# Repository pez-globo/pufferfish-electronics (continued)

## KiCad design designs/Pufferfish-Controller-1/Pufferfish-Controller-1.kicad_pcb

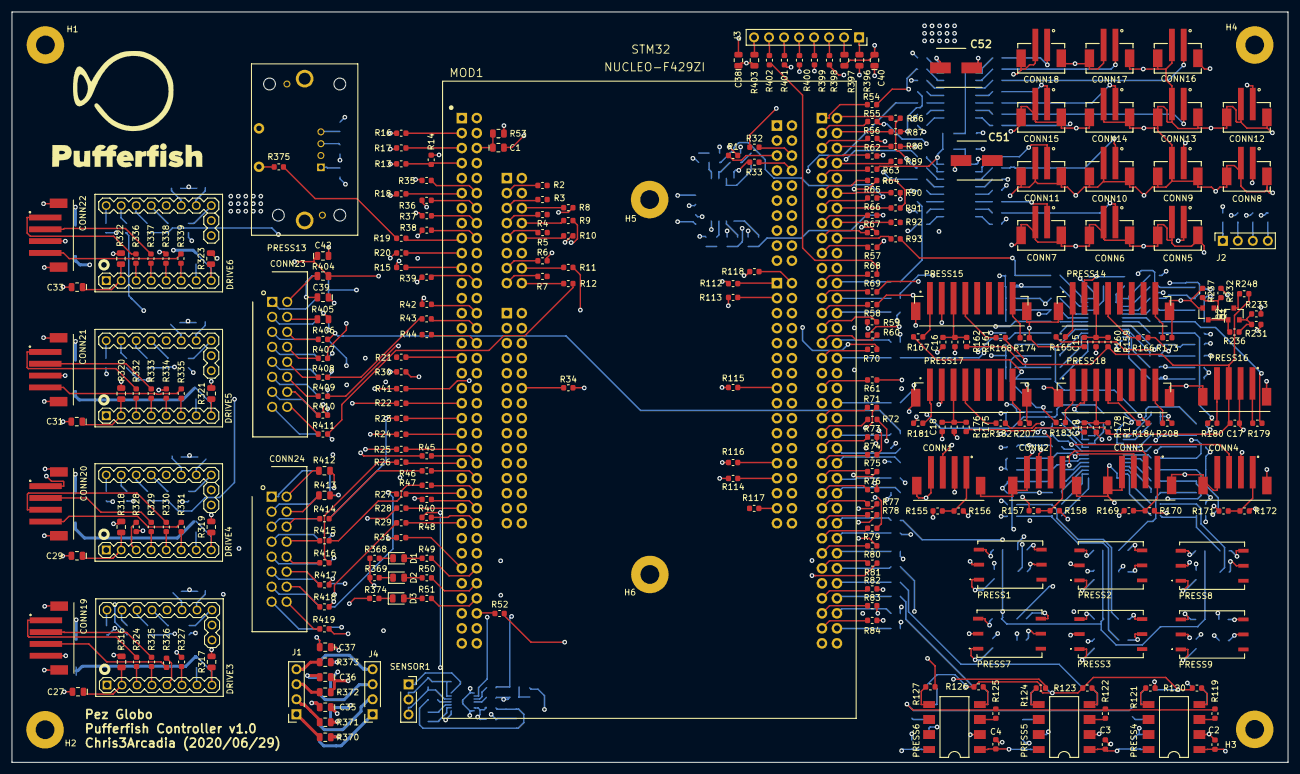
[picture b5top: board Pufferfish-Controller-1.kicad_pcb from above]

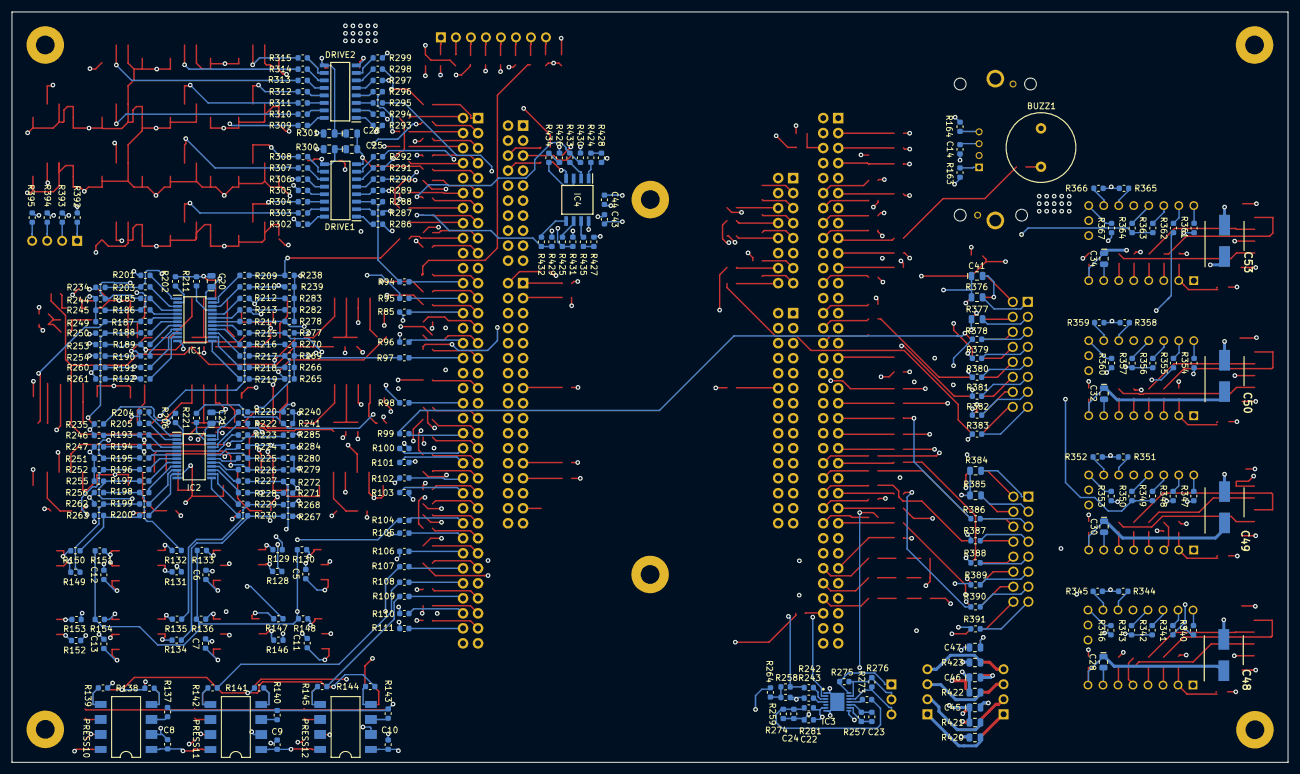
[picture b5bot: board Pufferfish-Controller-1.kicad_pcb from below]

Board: 6 copper layers, 216.0 x 127.0 mm, 559 parts (276 on the bottom side), 537 nets.

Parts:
BUZZ1: BUZZER-12MM
C1, C20, C21, C25, C26, C27, C28, C29, C30, C31, C32, C33, C34, C35, C36, C37, C38, C39, C40, C41, C42, C45, C46, C47: CAP_POLAR_SMD_0805
C2, C3, C4, C5, C6, C7, C8, C9, C10, C11, C12, C13, C14, C15, C16, C17, C18, C19, C22, C23, C24, C43, C44: CAP_SMD_0603
C48, C49, C50, C51, C52, C53: UCQ1E101MCL1GS; CAPAE660X820N
CONN1, CONN2, CONN3, CONN4, CONN19, CONN20, CONN21, CONN22: B4B-PH-SM4-TB(LF)(SN); JST_B4B-PH-SM4-TB
CONN5, CONN6, CONN7, CONN8, CONN9, CONN10, CONN11, CONN12, CONN13, CONN14, CONN15, CONN16, CONN17, CONN18: B2B-PH-SM4-TB(LF)(SN); JST_B2B-PH-SM4-TB
CONN23, CONN24: 5103308-3; SHDR16W66P254_2X8
D1, D2, D3: LED_SMD_0805
DRIVE1, DRIVE2: TPL7407LADR; SOIC127P600X175-16N
DRIVE3, DRIVE4, DRIVE5, DRIVE6: TMC2209-SilentStepStick; MODULE_TMC2209_SilentStepStick
H1, H2, H3, H4, H5, H6: STANDOFF_ELECTRICAL; STANDOFF-ELECTRICAL-NOTHERMALS
IC1, IC2: TCA9548APWR; SOP65P640X120-24N
IC3: LMP91000SDE; SON50P400X400X80-15N
IC4: W25Q16JVSSIQ; SOIC127P790X216-8N
J1, J2, J4: TERMINAL_SCREW_4_2.54mm; TERMINAL_PIN_4_2.54mm
J3: TERMINAL_SCREW_8_2.54mm; TERMINAL_PIN_8_2.54mm
L1: LOGO_PUFFERFISH
MOD1: NUCLEO-F429ZI; MODULE_NUCLEO-F429ZI
PRESS1, PRESS2, PRESS3, PRESS9: ABPMAND001PG2A3; ABPMANN030PG2A3
PRESS4, PRESS5, PRESS6: HSCMRRN100MDSA3; PRESSURE_HSC_SOIC-8
PRESS7, PRESS8: ABPMANN030PG2A3
PRESS10, PRESS11, PRESS12: HSCMRRN060PDSA3; PRESSURE_HSC_SOIC-8
PRESS13: SDP810-125PA; PRESSURE_SDP81x
PRESS14, PRESS15, PRESS17, PRESS18: SENSIRION_EK-P4_JST; SENSIRION_EK-P_JST
PRESS16: SENSIRION_SFM3000_JST
Q1: 2N7002E; SOT-23
Q2: TP0610T; SOT-23
R1, R2, R3, R4, R5, R6, R7, R8, R9, R10, R11, R12, R15, R16, R18, R19, R20, R21, R22, R23, R24, R25, R26, R27, R28, R29, R30, R31, R32, R33, R34, R40, R41, R42, R43, R44, R45, R46, R47, R48, R49, R50, R51, R52, R54, R55, R56, R57, R58, R59, R60, R61, R62, R63, R64, R65, R66, R67, R68, R69, R70, R71, R72, R73, R74, R75, R76, R77, R78, R79, R80, R81, R82, R83, R84, R85, R86, R87, R88, R89, R90, R91, R92, R93, R94, R95, R96, R97, R98, R99, R100, R101, R102, R103, R104, R105, R106, R107, R108, R109, R110, R111, R112, R113, R114, R115, R116, R117, R118, R119, R120, R121, R122, R123, R124, R125, R126, R127, R128, R129, R130, R131, R132, R133, R134, R135, R136, R137, R138, R139, R140, R141, R142, R143, R144, R145, R146, R147, R148, R149, R150, R151, R152, R153, R154, R156, R158, R160, R162, R163, R164, R165, R166, R167, R168, R170, R172, R173, R174, R176, R178, R179, R180, R181, R182, R183, R184, R185, R186, R187, R188, R189, R190, R191, R192, R193, R194, R195, R196, R197, R198, R199, R200, R201, R202, R203, R204, R205, R206, R207, R208, R209, R210, R211, R212, R213, R214, R215, R216, R217, R218, R219, R220, R221, R222, R223, R224, R225, R226, R227, R228, R229, R230, R231, R232, R242, R243, R248, R264, R273, R286, R287, R288, R289, R290, R291, R292, R293, R294, R295, R296, R297, R298, R299, R302, R303, R304, R305, R306, R307, R308, R309, R310, R311, R312, R313, R314, R315, R324, R325, R326, R327, R328, R329, R330, R331, R332, R333, R334, R335, R336, R337, R338, R339, R340, R341, R342, R343, R344, R345, R346, R347, R348, R349, R350, R351, R352, R353, R354, R355, R356, R357, R358, R359, R360, R361, R362, R363, R364, R365, R366, R367, R378, R379, R380, R381, R382, R383, R386, R387, R388, R389, R390, R391, R392, R393, R394, R395, R398, R399, R400, R401, R402, R406, R407, R408, R409, R410, R411, R414, R415, R416, R417, R418, R419, R424, R425, R432, R433, R434, R435: SHORT_SMD_0603
R13, R14, R17, R35, R36, R37, R38, R39, R155, R157, R159, R161, R169, R171, R175, R177, R233, R234, R235, R236, R237, R238, R239, R240, R241, R244, R245, R246, R247, R249, R250, R251, R252, R253, R254, R255, R256, R257, R258, R259, R260, R261, R262, R263, R265, R266, R267, R268, R269, R270, R271, R272, R274, R275, R276, R277, R278, R279, R280, R281, R282, R283, R284, R285, R368, R369, R374, R375, R426, R427, R428, R429, R430, R431: RES_SMD_0603
R53, R300, R301, R316, R317, R318, R319, R320, R321, R322, R323, R370, R371, R372, R373, R376, R377, R384, R385, R396, R397, R403, R404, R405, R412, R413, R420, R421, R422, R423: SHORT_SMD_0805
SENSOR1: MAXTEC_Max-12c; TERMINAL_PIN_3_2.54mm

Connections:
3.3V: C2.2, C3.2, C4.2, C5.2, C6.2, C7.2, C8.2, C9.2, C10.2, C11.2, C12.2, C13.2, C14.1, C20.1, C21.1, C35.1, C38.1, C39.1, C43.2, C44.2, IC1.24, IC2.24, IC4.8, PRESS1.2, PRESS2.2, PRESS3.2, PRESS4.2, PRESS5.2, PRESS6.2, PRESS7.2, PRESS8.2, PRESS9.2, PRESS10.2, PRESS11.2, PRESS12.2, PRESS13.2, R13.2, R17.2, R35.1, R37.1, R156.2, R158.2, R160.2, R162.2, R170.2, R172.2, R176.2, R178.2, R233.2, R234.1, R235.1, R238.1, R239.1, R240.1, R241.1, R244.1, R245.1, R246.1, R247.1, R249.1, R250.2, R251.1, R252.2, R253.1, R254.2, R255.1, R256.2, R260.1, R261.2, R262.1, R263.2, R264.2, R265.1, R266.2, R267.1, R268.2, R269.1, R270.2, R271.1, R272.2, R277.1, R278.2, R279.1, R280.2, R282.1, R283.2, R284.1, R285.2, R316.2, R318.2, R320.2, R322.2, R371.2, R403.2, R405.1, R426.1, R427.1, R428.1, R429.2, R430.2, R431.2
5V: C22.2, C36.1, C40.1, C41.1, C45.1, IC3.6, R32.1, R38.1, R53.1, R62.2, R112.2, R155.2, R157.2, R169.2, R171.2, R231.1, R281.1, R372.2, R376.2, R396.2, R421.2
12V: C37.1, C42.1, C46.1, C47.1, R39.1, R300.2, R301.2, R317.2, R319.2, R321.2, R323.2, R373.2, R404.1, R422.2, R423.2
ALARM1_HIGH: R118.1, R409.1
ALARM1_LOW: R1.2, R407.1
ALARM1_MED: R43.1, R408.1
ALARM2_CNTRL: R85.2, R378.2
BAT-CHARGE-EN: R47.1, R415.1
BAT-MEAS-ANALOG: R40.2, R412.1
BAT-MEAS-EN: R46.1, R414.1
BUZZ1_EN: R19.2, R375.2
CPU_UART_CLK: R68.2, R402.2
CPU_UART_CTS: R91.1, R401.2
CPU_UART_RTS: R90.1, R400.2
CPU_UART_RX: R70.2, R399.2
CPU_UART_TX: R67.2, R398.2
DRIVE1_CH1_EN: R61.1, R286.2
DRIVE1_CH2_EN: R60.1, R287.2
DRIVE1_CH3_EN: R94.1, R288.2
DRIVE1_CH4_EN: R58.1, R289.2
DRIVE1_CH5_EN: R59.1, R290.2
DRIVE1_CH6_EN: R86.1, R291.2
DRIVE1_CH7_EN: R15.1, R292.2
DRIVE2_CH1_EN: R100.1, R293.2
DRIVE2_CH2_EN: R101.1, R294.2
DRIVE2_CH3_EN: R42.1, R295.2
DRIVE2_CH4_EN: R87.1, R296.2
DRIVE2_CH5_EN: R57.1, R297.2
DRIVE2_CH6_EN: R54.1, R298.2
DRIVE2_CH7_EN: R95.1, R299.2
EXT_MEM_CS: R424.2, R428.2
EXT_MEM_HOLD: R427.2, R435.1
EXT_MEM_PROTECT: R426.2, R434.1
GND: BUZZ1.-, C1.2, C2.1, C3.1, C4.1, C5.1, C6.1, C7.1, C8.1, C9.1, C10.1, C11.1, C12.1, C13.1, C14.2, C15.2, C16.2, C17.2, C18.2, C19.2, C20.2, C21.2, C22.1, C24.2, C25.2, C26.2, C27.2, C28.2, C29.2, C30.2, C31.2, C32.2, C33.2, C34.2, C35.2, C36.2, C37.2, C38.2, C39.2, C40.2, C41.2, C42.2, C43.1, C44.1, C45.2, C46.2, C47.2, C48.2, C49.2, C50.2, C51.2, C52.2, C53.2, CONN1.4, CONN1.5, CONN1.6, CONN2.4, CONN2.5, CONN2.6, CONN3.4, CONN3.5, CONN3.6, CONN4.4, CONN4.5, CONN4.6, CONN5.2, CONN5.3, CONN5.4, CONN6.2, CONN6.3, CONN6.4, CONN7.2, CONN7.3, CONN7.4, CONN8.2, CONN8.3, CONN8.4, CONN9.2, CONN9.3, CONN9.4, CONN10.2, CONN10.3, CONN10.4, CONN11.2, CONN11.3, CONN11.4, CONN12.2, CONN12.3, CONN12.4, CONN13.2, CONN13.3, CONN13.4, CONN14.2, CONN14.3, CONN14.4, CONN15.2, CONN15.3, CONN15.4, CONN16.2, CONN16.3, CONN16.4, CONN17.2, CONN17.3, CONN17.4, CONN18.2, CONN18.3, CONN18.4, CONN19.5, CONN19.6, CONN20.5, CONN20.6, CONN21.5, CONN21.6, CONN22.5, CONN22.6, DRIVE1.8, DRIVE2.8, DRIVE3.1, DRIVE3.7, DRIVE4.1, DRIVE4.7, DRIVE5.1, DRIVE5.7, DRIVE6.1, DRIVE6.7, H1.P1, H2.P1, H3.P1, H4.P1, H5.P1, H6.P1, IC1.12, IC2.12, IC3.1, IC3.7, IC3.15, IC4.4, PRESS1.1, PRESS2.1, PRESS3.1, PRESS4.1, PRESS5.1, PRESS6.1, PRESS7.1, PRESS8.1, PRESS9.1, PRESS10.1, PRESS11.1, PRESS12.1, PRESS13.3, PRESS14.2, PRESS14.9, PRESS14.10, PRESS15.2, PRESS15.9, PRESS15.10, PRESS16.2, PRESS16.5, PRESS16.6, PRESS17.2, PRESS17.9, PRESS17.10, PRESS18.2, PRESS18.9, PRESS18.10, Q1.2, R6.2, R14.2, R20.2, R33.1, R34.2, R36.1, R63.2, R96.1, R113.2, R114.2, R173.2, R174.2, R201.2, R202.2, R204.2, R205.2, R207.2, R208.2, R211.1, R222.1, R237.1, R274.1, R344.1, R345.1, R351.1, R352.1, R358.1, R359.1, R365.1, R366.1, R368.2, R369.2, R370.2, R374.2, R377.2, R384.2, R385.2, R395.2, R397.2, R413.1, R420.2
GPIO1: R88.1, R392.2
GPIO2: R97.1, R393.2
GPIO3: R98.1, R394.2
I2C1_RESET: R110.1, R203.2, R234.2
I2C1_SC0: R163.2, R186.1, R245.2
I2C1_SC1: R180.2, R188.1, R250.1
I2C1_SC2: R166.2, R190.1, R254.1
I2C1_SC3: R182.2, R192.1, R261.1
I2C1_SC4: R168.2, R218.1, R266.1
I2C1_SC5: R184.2, R216.1, R270.1
I2C1_SC6: CONN1.2, R214.1, R278.1
I2C1_SC7: CONN2.3, R212.1, R283.1
I2C1_SCL: R69.2, R210.1, R239.2
I2C1_SD0: R164.2, R185.1, R244.2
I2C1_SD1: R179.2, R187.1, R249.2
I2C1_SD2: R165.2, R189.1, R253.2
I2C1_SD3: R181.2, R191.1, R260.2
I2C1_SD4: R167.2, R219.1, R265.2
I2C1_SD5: R183.2, R217.1, R269.2
I2C1_SD6: CONN1.3, R215.1, R277.2
I2C1_SD7: CONN2.2, R213.1, R282.2
I2C1_SDA: R93.1, R209.1, R238.2
I2C2_RESET: R111.1, R206.2, R235.2
I2C2_SC0: R129.2, R194.1, R247.2
I2C2_SC1: R147.2, R196.1, R252.1
I2C2_SC2: R132.2, R198.1, R256.1
I2C2_SC3: R150.2, R200.1, R263.1
I2C2_SC4: R135.2, R229.1, R268.1
I2C2_SC5: R153.2, R227.1, R272.1
I2C2_SC6: CONN3.3, R225.1, R280.1
I2C2_SC7: CONN4.3, R223.1, R285.1
I2C2_SCL: R55.1, R221.1, R241.2
I2C2_SD0: R128.2, R193.1, R246.2
I2C2_SD1: R146.2, R195.1, R251.2
I2C2_SD2: R131.2, R197.1, R255.2
I2C2_SD3: R149.2, R199.1, R262.2
I2C2_SD4: R134.2, R230.1, R267.2
I2C2_SD5: R152.2, R228.1, R271.2
I2C2_SD6: CONN3.2, R226.1, R279.2
I2C2_SD7: CONN4.2, R224.1, R284.2
I2C2_SDA: R56.1, R220.1, R240.2
I2C3_SCL: R102.1, R242.2, R258.1
I2C3_SDA: R71.2, R243.2, R259.1
LED1_EN: D1.2, R49.1
LED2_EN: D2.2, R50.1
LED3_EN: D3.2, R51.1
LEDB_EN: R9.1, R380.2
LEDG_EN: R10.1, R381.2
LEDR_EN: R8.1, R379.2
LTC4421-PWR-nCH1: R30.2, R419.1
LTC4421-PWR-nCH2: R41.2, R418.1
LTC4421-PWR-nDISABLE1: R24.2, R388.2
LTC4421-PWR-nDISABLE2: R25.2, R389.2
LTC4421-PWR-nFAULT1: R27.2, R390.2
LTC4421-PWR-nFAULT2: R28.2, R391.2
LTC4421-PWR-nVALID1: R22.2, R387.2
LTC4421-PWR-nVALID2: R23.2, R386.2
MOTOR1_DIR: R72.2, R340.1
MOTOR1_EN: R83.2, R346.1
MOTOR1_STEP: R73.2, R341.1
MOTOR1_UART: R29.2, R342.1, R343.1
MOTOR2_DIR: R75.2, R354.1
MOTOR2_EN: R74.2, R360.1
MOTOR2_STEP: R76.2, R355.1
MOTOR2_UART: R16.2, R356.1, R357.1
MOTOR3_DIR: R78.2, R347.1
MOTOR3_EN: R77.2, R353.1
MOTOR3_STEP: R79.2, R348.1
MOTOR3_UART: R18.2, R349.1, R350.1
MOTOR4_DIR: R81.2, R361.1
MOTOR4_EN: R80.2, R367.1
MOTOR4_STEP: R82.2, R362.1
MOTOR4_UART: R31.2, R363.1, R364.1
unnamed: BUZZ1.+, R375.1
unnamed: C1.1, MOD1.CN11_6, R53.2
unnamed: C15.1, PRESS14.3, R159.1, R160.1
unnamed: C16.1, PRESS15.3, R161.1, R162.1
unnamed: C18.1, PRESS17.3, R175.1, R176.1
unnamed: C19.1, PRESS18.3, R177.1, R178.1
unnamed: C23.1, IC3.10, R257.2
unnamed: C23.2, IC3.9, R257.1
unnamed: C24.1, R273.1, R274.2, R281.2
unnamed: C25.1, C51.1, DRIVE1.9, R300.1
unnamed: C26.1, C52.1, DRIVE2.9, R301.1
unnamed: C27.1, DRIVE3.2, R316.1
unnamed: C28.1, C48.1, DRIVE3.8, R317.1
unnamed: C29.1, DRIVE4.2, R318.1
unnamed: C30.1, C49.1, DRIVE4.8, R319.1
unnamed: C31.1, DRIVE5.2, R320.1
unnamed: C32.1, C50.1, DRIVE5.8, R321.1
unnamed: C33.1, DRIVE6.2, R322.1
unnamed: C34.1, C53.1, DRIVE6.8, R323.1
unnamed: CONN1.1, R155.1, R156.1
unnamed: CONN2.1, R157.1, R158.1
unnamed: CONN3.1, R169.1, R170.1
unnamed: CONN4.1, R171.1, R172.1
unnamed: CONN5.1, R302.1
unnamed: CONN6.1, R303.1
unnamed: CONN7.1, R304.1
unnamed: CONN8.1, R305.1
unnamed: CONN9.1, R306.1
unnamed: CONN10.1, R307.1
unnamed: CONN11.1, R308.1
unnamed: CONN12.1, R309.1
unnamed: CONN13.1, R310.1
unnamed: CONN14.1, R311.1
unnamed: CONN15.1, R312.1
unnamed: CONN16.1, R313.1
unnamed: CONN17.1, R314.1
unnamed: CONN18.1, R315.1
unnamed: CONN19.1, R324.2
unnamed: CONN19.2, R325.2
unnamed: CONN19.3, R326.2
unnamed: CONN19.4, R327.2
unnamed: CONN20.1, R328.2
unnamed: CONN20.2, R329.2
unnamed: CONN20.3, R330.2
unnamed: CONN20.4, R331.2
unnamed: CONN21.1, R332.2
unnamed: CONN21.2, R333.2
unnamed: CONN21.3, R334.2
unnamed: CONN21.4, R335.2
unnamed: CONN22.1, R336.2
unnamed: CONN22.2, R337.2
unnamed: CONN22.3, R338.2
unnamed: CONN22.4, R339.2
unnamed: CONN23.1, R376.1
unnamed: CONN23.2, R404.2
unnamed: CONN23.3, R377.1
unnamed: CONN23.4, R405.2
unnamed: CONN23.5, R378.1
unnamed: CONN23.6, R406.2
unnamed: CONN23.7, R379.1
unnamed: CONN23.8, R407.2
unnamed: CONN23.9, R380.1
unnamed: CONN23.10, R408.2
unnamed: CONN23.11, R381.1
unnamed: CONN23.12, R409.2
unnamed: CONN23.13, R382.1
unnamed: CONN23.14, R410.2
unnamed: CONN23.15, R383.1
unnamed: CONN23.16, R411.2
unnamed: CONN24.1, R384.1
unnamed: CONN24.2, R412.2
unnamed: CONN24.3, R385.1
unnamed: CONN24.4, R413.2
unnamed: CONN24.5, R386.1
unnamed: CONN24.6, R414.2
unnamed: CONN24.7, R387.1
unnamed: CONN24.8, R415.2
unnamed: CONN24.9, R388.1
unnamed: CONN24.10, R416.2
unnamed: CONN24.11, R389.1
unnamed: CONN24.12, R417.2
unnamed: CONN24.13, R390.1
unnamed: CONN24.14, R418.2
unnamed: CONN24.15, R391.1
unnamed: CONN24.16, R419.2
unnamed: D1.1, R368.1
unnamed: D2.1, R369.1
unnamed: D3.1, R374.1
unnamed: DRIVE1.1, R286.1
unnamed: DRIVE1.2, R287.1
unnamed: DRIVE1.3, R288.1
unnamed: DRIVE1.4, R289.1
unnamed: DRIVE1.5, R290.1
unnamed: DRIVE1.6, R291.1
unnamed: DRIVE1.7, R292.1
unnamed: DRIVE1.10, R308.2
unnamed: DRIVE1.11, R307.2
unnamed: DRIVE1.12, R306.2
unnamed: DRIVE1.13, R305.2
unnamed: DRIVE1.14, R304.2
unnamed: DRIVE1.15, R303.2
unnamed: DRIVE1.16, R302.2
unnamed: DRIVE2.1, R293.1
unnamed: DRIVE2.2, R294.1
unnamed: DRIVE2.3, R295.1
unnamed: DRIVE2.4, R296.1
unnamed: DRIVE2.5, R297.1
unnamed: DRIVE2.6, R298.1
unnamed: DRIVE2.7, R299.1
unnamed: DRIVE2.10, R315.2
unnamed: DRIVE2.11, R314.2
unnamed: DRIVE2.12, R313.2
unnamed: DRIVE2.13, R312.2
unnamed: DRIVE2.14, R311.2
unnamed: DRIVE2.15, R310.2
unnamed: DRIVE2.16, R309.2
unnamed: DRIVE3.3, R324.1
unnamed: DRIVE3.4, R325.1
unnamed: DRIVE3.5, R326.1
unnamed: DRIVE3.6, R327.1
unnamed: DRIVE3.9, R340.2
unnamed: DRIVE3.10, R341.2
unnamed: DRIVE3.11, R342.2
unnamed: DRIVE3.12, R343.2
unnamed: DRIVE3.14, R344.2
unnamed: DRIVE3.15, R345.2
unnamed: DRIVE3.16, R346.2
unnamed: DRIVE4.3, R328.1
unnamed: DRIVE4.4, R329.1
unnamed: DRIVE4.5, R330.1
unnamed: DRIVE4.6, R331.1
unnamed: DRIVE4.9, R347.2
unnamed: DRIVE4.10, R348.2
unnamed: DRIVE4.11, R349.2
unnamed: DRIVE4.12, R350.2
unnamed: DRIVE4.14, R351.2
unnamed: DRIVE4.15, R352.2
unnamed: DRIVE4.16, R353.2
unnamed: DRIVE5.3, R332.1
unnamed: DRIVE5.4, R333.1
unnamed: DRIVE5.5, R334.1
unnamed: DRIVE5.6, R335.1
unnamed: DRIVE5.9, R354.2
unnamed: DRIVE5.10, R355.2
unnamed: DRIVE5.11, R356.2
unnamed: DRIVE5.12, R357.2
unnamed: DRIVE5.14, R358.2
unnamed: DRIVE5.15, R359.2
unnamed: DRIVE5.16, R360.2
unnamed: DRIVE6.3, R336.1
unnamed: DRIVE6.4, R337.1
unnamed: DRIVE6.5, R338.1
unnamed: DRIVE6.6, R339.1
unnamed: DRIVE6.9, R361.2
unnamed: DRIVE6.10, R362.2
unnamed: DRIVE6.11, R363.2
unnamed: DRIVE6.12, R364.2
unnamed: DRIVE6.14, R365.2
unnamed: DRIVE6.15, R366.2
unnamed: DRIVE6.16, R367.2
unnamed: IC1.1, R201.1
unnamed: IC1.2, R202.1
unnamed: IC1.3, R203.1
unnamed: IC1.4, R185.2
unnamed: IC1.5, R186.2
unnamed: IC1.6, R187.2
unnamed: IC1.7, R188.2
unnamed: IC1.8, R189.2
unnamed: IC1.9, R190.2
unnamed: IC1.10, R191.2
unnamed: IC1.11, R192.2
unnamed: IC1.13, R219.2
unnamed: IC1.14, R218.2
unnamed: IC1.15, R217.2
unnamed: IC1.16, R216.2
unnamed: IC1.17, R215.2
unnamed: IC1.18, R214.2
unnamed: IC1.19, R213.2
unnamed: IC1.20, R212.2
unnamed: IC1.21, R211.2
unnamed: IC1.22, R210.2
unnamed: IC1.23, R209.2
unnamed: IC2.1, R204.1
unnamed: IC2.2, R205.1
unnamed: IC2.3, R206.1
unnamed: IC2.4, R193.2
unnamed: IC2.5, R194.2
unnamed: IC2.6, R195.2
unnamed: IC2.7, R196.2
unnamed: IC2.8, R197.2
unnamed: IC2.9, R198.2
unnamed: IC2.10, R199.2
unnamed: IC2.11, R200.2
unnamed: IC2.13, R230.2
unnamed: IC2.14, R229.2
unnamed: IC2.15, R228.2
unnamed: IC2.16, R227.2
unnamed: IC2.17, R226.2
unnamed: IC2.18, R225.2
unnamed: IC2.19, R224.2
unnamed: IC2.20, R223.2
unnamed: IC2.21, R222.2
unnamed: IC2.22, R221.2
unnamed: IC2.23, R220.2
unnamed: IC3.3, R242.1
unnamed: IC3.4, R243.1
unnamed: IC3.11, R273.2
unnamed: IC3.12, R276.1, SENSOR1.3
unnamed: IC3.13, R275.1, R276.2, SENSOR1.2
unnamed: IC3.14, R275.2, SENSOR1.1
unnamed: IC4.1, R424.1
unnamed: IC4.2, R433.2
unnamed: IC4.3, R434.2
unnamed: IC4.5, R432.2
unnamed: IC4.6, R425.1
unnamed: IC4.7, R435.2
unnamed: J1.1, R370.1
unnamed: J1.2, R371.1
unnamed: J1.3, R372.1
unnamed: J1.4, R373.1
unnamed: J2.1, R392.1
unnamed: J2.2, R393.1
unnamed: J2.3, R394.1
unnamed: J2.4, R395.1
unnamed: J3.1, R396.1
unnamed: J3.2, R397.1
unnamed: J3.3, R398.1
unnamed: J3.4, R399.1
unnamed: J3.5, R400.1
unnamed: J3.6, R401.1
unnamed: J3.7, R402.1
unnamed: J3.8, R403.1
unnamed: J4.1, R420.1
unnamed: J4.2, R421.1
unnamed: J4.3, R422.1
unnamed: J4.4, R423.1
unnamed: MOD1.CN7_5, R1.1
unnamed: MOD1.CN7_6, R32.2
unnamed: MOD1.CN7_8, R33.2
unnamed: MOD1.CN8_3, R2.1
unnamed: MOD1.CN8_5, R3.1
unnamed: MOD1.CN8_6, R8.2
unnamed: MOD1.CN8_7, R4.1
unnamed: MOD1.CN8_8, R9.2
unnamed: MOD1.CN8_9, R5.1
unnamed: MOD1.CN8_10, R10.2
unnamed: MOD1.CN8_11, MOD1.CN8_13, R6.1
unnamed: MOD1.CN8_14, R11.2
unnamed: MOD1.CN8_15, R7.1
unnamed: MOD1.CN8_16, R12.2
unnamed: MOD1.CN9_12, MOD1.CN9_23, R34.1
unnamed: MOD1.CN10_1, R112.1
unnamed: MOD1.CN10_2, R118.2
unnamed: MOD1.CN10_3, R113.1
unnamed: MOD1.CN10_15, R115.1
unnamed: MOD1.CN10_5, MOD1.CN10_17, MOD1.CN10_22, MOD1.CN10_27, R114.1
unnamed: MOD1.CN10_25, R116.1
unnamed: MOD1.CN10_31, R117.1
unnamed: MOD1.CN11_3, R16.1
unnamed: MOD1.CN11_5, R17.1
unnamed: MOD1.CN11_7, R13.1, R14.1
unnamed: MOD1.CN11_11, R18.1
unnamed: MOD1.CN11_12, R35.2
unnamed: MOD1.CN11_14, R36.2
unnamed: MOD1.CN11_16, R37.2
unnamed: MOD1.CN11_17, R19.1
unnamed: MOD1.CN11_18, R38.2
unnamed: MOD1.CN11_8, MOD1.CN11_19, MOD1.CN11_20, MOD1.CN11_22, MOD1.CN11_49, MOD1.CN11_60, MOD1.CN11_71, MOD1.CN11_72, R20.1
unnamed: MOD1.CN11_21, R15.2
unnamed: MOD1.CN11_24, R39.2
unnamed: MOD1.CN11_28, R42.2
unnamed: MOD1.CN11_30, R43.2
unnamed: MOD1.CN11_32, R44.2
unnamed: MOD1.CN11_33, R21.1
unnamed: MOD1.CN11_39, R22.1
unnamed: MOD1.CN11_41, R23.1
unnamed: MOD1.CN11_43, R24.1
unnamed: MOD1.CN11_45, R25.1
unnamed: MOD1.CN11_47, R26.1
unnamed: MOD1.CN11_48, R45.2
unnamed: MOD1.CN11_50, R46.2
unnamed: MOD1.CN11_51, R27.1
unnamed: MOD1.CN11_52, R47.2
unnamed: MOD1.CN11_53, R28.1
unnamed: MOD1.CN11_54, R40.1
unnamed: MOD1.CN11_55, R29.1
unnamed: MOD1.CN11_56, R48.2
unnamed: MOD1.CN11_58, R41.1
unnamed: MOD1.CN11_59, R30.1
unnamed: MOD1.CN11_61, R31.1
unnamed: MOD1.CN11_62, R49.2
unnamed: MOD1.CN11_64, R50.2
unnamed: MOD1.CN11_66, R51.2
unnamed: MOD1.CN11_68, R52.2
unnamed: MOD1.CN12_1, R54.2
unnamed: MOD1.CN12_2, R86.2
unnamed: MOD1.CN12_3, R55.2
unnamed: MOD1.CN12_4, R87.2
unnamed: MOD1.CN12_5, R56.2
unnamed: MOD1.CN12_6, R88.2
unnamed: MOD1.CN12_7, R62.1
unnamed: MOD1.CN12_8, R89.2
unnamed: MOD1.CN12_11, R64.1
unnamed: MOD1.CN12_12, R90.2
unnamed: MOD1.CN12_13, R65.1
unnamed: MOD1.CN12_14, R91.2
unnamed: MOD1.CN12_15, R66.1
unnamed: MOD1.CN12_16, R92.2
unnamed: MOD1.CN12_17, R67.1
unnamed: MOD1.CN12_18, R93.2
unnamed: MOD1.CN12_19, R57.2
unnamed: MOD1.CN12_9, MOD1.CN12_20, MOD1.CN12_39, MOD1.CN12_54, MOD1.CN12_63, MOD1.CN12_71, MOD1.CN12_72, R63.1
unnamed: MOD1.CN12_23, R68.1
unnamed: MOD1.CN12_24, R94.2
unnamed: MOD1.CN12_25, R69.1
unnamed: MOD1.CN12_26, R95.2
unnamed: MOD1.CN12_27, R58.2
unnamed: MOD1.CN12_28, R85.1
unnamed: MOD1.CN12_29, R59.2
unnamed: MOD1.CN12_31, R60.2
unnamed: MOD1.CN12_32, R96.2
unnamed: MOD1.CN12_33, R70.1
unnamed: MOD1.CN12_34, R97.2
unnamed: MOD1.CN12_37, R61.2
unnamed: MOD1.CN12_40, R98.2
unnamed: MOD1.CN12_41, R71.1
unnamed: MOD1.CN12_43, R72.1
unnamed: MOD1.CN12_44, R99.2
unnamed: MOD1.CN12_45, R73.1
unnamed: MOD1.CN12_46, R100.2
unnamed: MOD1.CN12_47, R74.1
unnamed: MOD1.CN12_48, R101.2
unnamed: MOD1.CN12_49, R75.1
unnamed: MOD1.CN12_50, R102.2
unnamed: MOD1.CN12_51, R76.1
unnamed: MOD1.CN12_52, R103.2
unnamed: MOD1.CN12_53, R77.1
unnamed: MOD1.CN12_55, R78.1
unnamed: MOD1.CN12_56, R104.2
unnamed: MOD1.CN12_57, R79.1
unnamed: MOD1.CN12_58, R105.2
unnamed: MOD1.CN12_59, R80.1
unnamed: MOD1.CN12_60, R106.2
unnamed: MOD1.CN12_61, R81.1
unnamed: MOD1.CN12_62, R107.2
unnamed: MOD1.CN12_64, R108.2
unnamed: MOD1.CN12_65, R82.1
unnamed: MOD1.CN12_66, R109.2
unnamed: MOD1.CN12_67, R83.1
unnamed: MOD1.CN12_68, R110.2
unnamed: MOD1.CN12_69, R84.1
unnamed: MOD1.CN12_70, R111.2
unnamed: PRESS1.3, R130.1
unnamed: PRESS1.5, R128.1
unnamed: PRESS1.6, R129.1
unnamed: PRESS2.3, R133.1
unnamed: PRESS2.5, R131.1
unnamed: PRESS2.6, R132.1
unnamed: PRESS3.3, R136.1
unnamed: PRESS3.5, R134.1
unnamed: PRESS3.6, R135.1
unnamed: PRESS4.3, R119.1
unnamed: PRESS4.4, R120.1
unnamed: PRESS4.5, R121.1
unnamed: PRESS5.3, R122.1
unnamed: PRESS5.4, R123.1
unnamed: PRESS5.5, R124.1
unnamed: PRESS6.3, R125.1
unnamed: PRESS6.4, R126.1
unnamed: PRESS6.5, R127.1
unnamed: PRESS7.3, R148.1
unnamed: PRESS7.5, R146.1
unnamed: PRESS7.6, R147.1
unnamed: PRESS8.3, R151.1
unnamed: PRESS8.5, R149.1
unnamed: PRESS8.6, R150.1
unnamed: PRESS9.3, R154.1
unnamed: PRESS9.5, R152.1
unnamed: PRESS9.6, R153.1
unnamed: PRESS10.3, R137.1
unnamed: PRESS10.4, R138.1
unnamed: PRESS10.5, R139.1
unnamed: PRESS11.3, R140.1
unnamed: PRESS11.4, R141.1
unnamed: PRESS11.5, R142.1
unnamed: PRESS12.3, R143.1
unnamed: PRESS12.4, R144.1
unnamed: PRESS12.5, R145.1
unnamed: PRESS13.1, R163.1
unnamed: PRESS13.4, R164.1
unnamed: PRESS14.1, R165.1
unnamed: PRESS14.4, R166.1
unnamed: PRESS14.8, R173.1
unnamed: PRESS15.1, R167.1
unnamed: PRESS15.4, R168.1
unnamed: PRESS15.8, R174.1
unnamed: PRESS16.1, R179.1
unnamed: PRESS16.4, R180.1
unnamed: PRESS17.1, R181.1
unnamed: PRESS17.4, R182.1
unnamed: PRESS17.8, R207.1
unnamed: PRESS18.1, R183.1
unnamed: PRESS18.4, R184.1
unnamed: PRESS18.8, R208.1
unnamed: Q1.1, R232.2, R237.2
unnamed: Q1.3, Q2.1, R236.1
unnamed: Q2.2, R231.2, R233.1, R236.2
unnamed: Q2.3, R248.1
unnamed: R258.2, R259.2, R264.1
PRESS1_EN: R104.1, R121.2
PRESS2_EN: R105.1, R124.2
PRESS3_EN: R106.1, R127.2
PRESS4_EN: R107.1, R139.2
PRESS5_EN: R108.1, R142.2
PRESS6_EN: R109.1, R145.2
PRESSX_EN: R52.1, R130.2, R133.2, R136.2, R148.2, R151.2, R154.2
PRESS_VDD: C17.1, PRESS16.3, R159.2, R161.2, R175.2, R177.2, R248.2
PRESS_VDD_EN: R84.2, R232.1
SENSE_O2_EN: IC3.2, R103.1
SENSE_O2_OUT: IC3.8, R48.1
SET_ALARM_EN: R11.1, R410.1
SET_EXTRA: R99.1, R406.1
SET_LOCK: R12.1, R411.1
SET_PWR_ON_OFF: R116.2, R383.2
SET_PWR_SRC: R115.2, R382.2
SPI1_MISO: R65.2, R119.2, R122.2, R125.2, R137.2, R140.2, R143.2, R430.1, R433.1
SPI1_MOSI: R66.2, R429.1, R432.1
SPI1_SCL: R64.2, R120.2, R123.2, R126.2, R138.2, R141.2, R144.2, R425.2, R431.1
VSYS-3V3-PGOOD: R26.2, R416.1
VSYS-5V0-PGOOD: R45.1, R417.1

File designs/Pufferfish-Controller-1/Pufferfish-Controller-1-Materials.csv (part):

"Source:","C:\Users\chris\Dropbox (Brown)\Ventilator\repositories\pufferfish-electronics\designs\Pufferfish-Controller-1\Pufferfish-Controller-1.sch"
"Date:","6/29/2020 4:31:52 PM"
"Tool:","Eeschema (5.1.6)-1"
"Component Count:","553"
"Ref","Value","Part","Footprint","Description","Vendor","Manufacturer","Datasheet","Tolerance","Resistance","Capacitance","Pressure"
"BUZZ1","BUZZER-12MM","Pufferfish:BUZZER-12MM","Pufferfish:BUZZER-12MM","Generic 12mm Buzzer","","","","","","",""
"C1","CAP_POLAR_SMD_0805","Pufferfish:CAP_POLAR_SMD_0805","Pufferfish:CAP_POLAR_SMD_0805","Polarized capacitor, small symbol, 0805, SMD, SMT","","","","?%","","47uF",""
"C2","CAP_SMD_0603","Pufferfish:CAP_SMD_0603","Pufferfish:CAP_SMD_0603","Unpolarized capacitor, small symbol, 0603, SMD, SMT","","","","?%","","1uF",""
"C3","CAP_SMD_0603","Pufferfish:CAP_SMD_0603","Pufferfish:CAP_SMD_0603","Unpolarized capacitor, small symbol, 0603, SMD, SMT","","","","?%","","1uF",""
"C4","CAP_SMD_0603","Pufferfish:CAP_SMD_0603","Pufferfish:CAP_SMD_0603","Unpolarized capacitor, small symbol, 0603, SMD, SMT","","","","?%","","1uF",""
"C5","CAP_SMD_0603","Pufferfish:CAP_SMD_0603","Pufferfish:CAP_SMD_0603","Unpolarized capacitor, small symbol, 0603, SMD, SMT","","","","?%","","1uF",""
"C6","CAP_SMD_0603","Pufferfish:CAP_SMD_0603","Pufferfish:CAP_SMD_0603","Unpolarized capacitor, small symbol, 0603, SMD, SMT","","","","?%","","1uF",""
"C7","CAP_SMD_0603","Pufferfish:CAP_SMD_0603","Pufferfish:CAP_SMD_0603","Unpolarized capacitor, small symbol, 0603, SMD, SMT","","","","?%","","1uF",""
"C8","CAP_SMD_0603","Pufferfish:CAP_SMD_0603","Pufferfish:CAP_SMD_0603","Unpolarized capacitor, small symbol, 0603, SMD, SMT","","","","?%","","1uF",""
"C9","CAP_SMD_0603","Pufferfish:CAP_SMD_0603","Pufferfish:CAP_SMD_0603","Unpolarized capacitor, small symbol, 0603, SMD, SMT","","","","?%","","1uF",""
"C10","CAP_SMD_0603","Pufferfish:CAP_SMD_0603","Pufferfish:CAP_SMD_0603","Unpolarized capacitor, small symbol, 0603, SMD, SMT","","","","?%","","1uF",""
"C11","CAP_SMD_0603","Pufferfish:CAP_SMD_0603","Pufferfish:CAP_SMD_0603","Unpolarized capacitor, small symbol, 0603, SMD, SMT","","","","?%","","1uF",""
"C12","CAP_SMD_0603","Pufferfish:CAP_SMD_0603","Pufferfish:CAP_SMD_0603","Unpolarized capacitor, small symbol, 0603, SMD, SMT","","","","?%","","1uF",""
"C13","CAP_SMD_0603","Pufferfish:CAP_SMD_0603","Pufferfish:CAP_SMD_0603","Unpolarized capacitor, small symbol, 0603, SMD, SMT","","","","?%","","1uF",""
"C14","CAP_SMD_0603","Pufferfish:CAP_SMD_0603","Pufferfish:CAP_SMD_0603","Unpolarized capacitor, small symbol, 0603, SMD, SMT","","","","?%","","1uF",""
"C15","CAP_SMD_0603","Pufferfish:CAP_SMD_0603","Pufferfish:CAP_SMD_0603","Unpolarized capacitor, small symbol, 0603, SMD, SMT","","","","?%","","1uF",""
"C16","CAP_SMD_0603","Pufferfish:CAP_SMD_0603","Pufferfish:CAP_SMD_0603","Unpolarized capacitor, small symbol, 0603, SMD, SMT","","","","?%","","1uF",""
"C17","CAP_SMD_0603","Pufferfish:CAP_SMD_0603","Pufferfish:CAP_SMD_0603","Unpolarized capacitor, small symbol, 0603, SMD, SMT","","","","?%","","1uF",""
"C18","CAP_SMD_0603","Pufferfish:CAP_SMD_0603","Pufferfish:CAP_SMD_0603","Unpolarized capacitor, small symbol, 0603, SMD, SMT","","","","?%","","1uF",""
"C19","CAP_SMD_0603","Pufferfish:CAP_SMD_0603","Pufferfish:CAP_SMD_0603","Unpolarized capacitor, small symbol, 0603, SMD, SMT","","","","?%","","1uF",""
"C20","CAP_POLAR_SMD_0805","Pufferfish:CAP_POLAR_SMD_0805","Pufferfish:CAP_POLAR_SMD_0805","Polarized capacitor, small symbol, 0805, SMD, SMT","","","","?%","","10uF",""
"C21","CAP_POLAR_SMD_0805","Pufferfish:CAP_POLAR_SMD_0805","Pufferfish:CAP_POLAR_SMD_0805","Polarized capacitor, small symbol, 0805, SMD, SMT","","","","?%","","10uF",""
"C22","CAP_SMD_0603","Pufferfish:CAP_SMD_0603","Pufferfish:CAP_SMD_0603","Unpolarized capacitor, small symbol, 0603, SMD, SMT","","","","?%","","1uF",""
"C23","CAP_SMD_0603","Pufferfish:CAP_SMD_0603","Pufferfish:CAP_SMD_0603","Unpolarized capacitor, small symbol, 0603, SMD, SMT","","","","?%","","DNP",""
"C24","CAP_SMD_0603","Pufferfish:CAP_SMD_0603","Pufferfish:CAP_SMD_0603","Unpolarized capacitor, small symbol, 0603, SMD, SMT","","","","?%","","1uF",""
"C25","CAP_POLAR_SMD_0805","Pufferfish:CAP_POLAR_SMD_0805","Pufferfish:CAP_POLAR_SMD_0805","Polarized capacitor, small symbol, 0805, SMD, SMT","","","","?%","","10uF",""
"C26","CAP_POLAR_SMD_0805","Pufferfish:CAP_POLAR_SMD_0805","Pufferfish:CAP_POLAR_SMD_0805","Polarized capacitor, small symbol, 0805, SMD, SMT","","","","?%","","10uF",""
"C27","CAP_POLAR_SMD_0805","Pufferfish:CAP_POLAR_SMD_0805","Pufferfish:CAP_POLAR_SMD_0805","Polarized capacitor, small symbol, 0805, SMD, SMT","","","","?%","","10uF",""
"C28","CAP_POLAR_SMD_0805","Pufferfish:CAP_POLAR_SMD_0805","Pufferfish:CAP_POLAR_SMD_0805","Polarized capacitor, small symbol, 0805, SMD, SMT","","","","?%","","10uF",""
"C29","CAP_POLAR_SMD_0805","Pufferfish:CAP_POLAR_SMD_0805","Pufferfish:CAP_POLAR_SMD_0805","Polarized capacitor, small symbol, 0805, SMD, SMT","","","","?%","","10uF",""
"C30","CAP_POLAR_SMD_0805","Pufferfish:CAP_POLAR_SMD_0805","Pufferfish:CAP_POLAR_SMD_0805","Polarized capacitor, small symbol, 0805, SMD, SMT","","","","?%","","10uF",""
"C31","CAP_POLAR_SMD_0805","Pufferfish:CAP_POLAR_SMD_0805","Pufferfish:CAP_POLAR_SMD_0805","Polarized capacitor, small symbol, 0805, SMD, SMT","","","","?%","","10uF",""
"C32","CAP_POLAR_SMD_0805","Pufferfish:CAP_POLAR_SMD_0805","Pufferfish:CAP_POLAR_SMD_0805","Polarized capacitor, small symbol, 0805, SMD, SMT","","","","?%","","10uF",""
"C33","CAP_POLAR_SMD_0805","Pufferfish:CAP_POLAR_SMD_0805","Pufferfish:CAP_POLAR_SMD_0805","Polarized capacitor, small symbol, 0805, SMD, SMT","","","","?%","","10uF",""
"C34","CAP_POLAR_SMD_0805","Pufferfish:CAP_POLAR_SMD_0805","Pufferfish:CAP_POLAR_SMD_0805","Polarized capacitor, small symbol, 0805, SMD, SMT","","","","?%","","10uF",""
"C35","CAP_POLAR_SMD_0805","Pufferfish:CAP_POLAR_SMD_0805","Pufferfish:CAP_POLAR_SMD_0805","Polarized capacitor, small symbol, 0805, SMD, SMT","","","","?%","","47uF",""
"C36","CAP_POLAR_SMD_0805","Pufferfish:CAP_POLAR_SMD_0805","Pufferfish:CAP_POLAR_SMD_0805","Polarized capacitor, small symbol, 0805, SMD, SMT","","","","?%","","47uF",""
"C37","CAP_POLAR_SMD_0805","Pufferfish:CAP_POLAR_SMD_0805","Pufferfish:CAP_POLAR_SMD_0805","Polarized capacitor, small symbol, 0805, SMD, SMT","","","","?%","","47uF",""
"C38","CAP_POLAR_SMD_0805","Pufferfish:CAP_POLAR_SMD_0805","Pufferfish:CAP_POLAR_SMD_0805","Polarized capacitor, small symbol, 0805, SMD, SMT","","","","?%","","47uF",""
"C39","CAP_POLAR_SMD_0805","Pufferfish:CAP_POLAR_SMD_0805","Pufferfish:CAP_POLAR_SMD_0805","Polarized capacitor, small symbol, 0805, SMD, SMT","","","","?%","","47uF",""
"C40","CAP_POLAR_SMD_0805","Pufferfish:CAP_POLAR_SMD_0805","Pufferfish:CAP_POLAR_SMD_0805","Polarized capacitor, small symbol, 0805, SMD, SMT","","","","?%","","47uF",""
"C41","CAP_POLAR_SMD_0805","Pufferfish:CAP_POLAR_SMD_0805","Pufferfish:CAP_POLAR_SMD_0805","Polarized capacitor, small symbol, 0805, SMD, SMT","","","","?%","","47uF",""
"C42","CAP_POLAR_SMD_0805","Pufferfish:CAP_POLAR_SMD_0805","Pufferfish:CAP_POLAR_SMD_0805","Polarized capacitor, small symbol, 0805, SMD, SMT","","","","?%","","47uF",""
"C43","CAP_SMD_0603","Pufferfish:CAP_SMD_0603","Pufferfish:CAP_SMD_0603","Unpolarized capacitor, small symbol, 0603, SMD, SMT","","","","?%","","100nF",""
"C44","CAP_SMD_0603","Pufferfish:CAP_SMD_0603","Pufferfish:CAP_SMD_0603","Unpolarized capacitor, small symbol, 0603, SMD, SMT","","","","?%","","1uF",""
"C45","CAP_POLAR_SMD_0805","Pufferfish:CAP_POLAR_SMD_0805","Pufferfish:CAP_POLAR_SMD_0805","Polarized capacitor, small symbol, 0805, SMD, SMT","","","","?%","","47uF",""
"C46","CAP_POLAR_SMD_0805","Pufferfish:CAP_POLAR_SMD_0805","Pufferfish:CAP_POLAR_SMD_0805","Polarized capacitor, small symbol, 0805, SMD, SMT","","","","?%","","47uF",""
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
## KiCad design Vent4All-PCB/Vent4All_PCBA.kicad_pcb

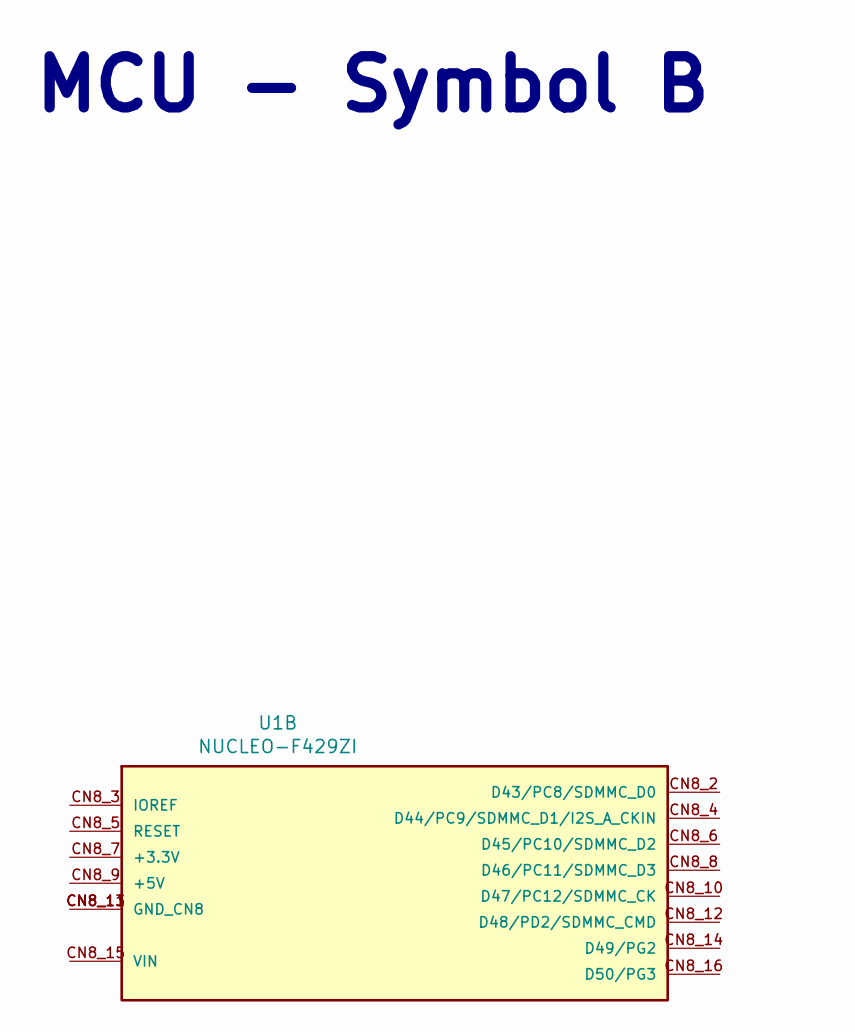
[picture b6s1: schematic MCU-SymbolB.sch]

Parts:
U1: NUCLEO-F429ZI; MODULE_NUCLEO-F429ZI

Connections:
unnamed: U1.CN8_11 (GND_CN8), U1.CN8_13 (GND_CN8)
unnamed: U1.CN9_12 (GND_CN9), U1.CN9_23 (GND_CN9)
unnamed: U1.CN10_5 (GND_CN10), U1.CN10_17 (GND_CN10), U1.CN10_22 (GND_CN10), U1.CN10_27 (GND_CN10)
unnamed: U1.CN11_8 (GND_CN11), U1.CN11_19 (GND_CN11), U1.CN11_20 (GND_CN11), U1.CN11_22 (GND_CN11), U1.CN11_49 (GND_CN11), U1.CN11_60 (GND_CN11), U1.CN11_71 (GND_CN11), U1.CN11_72 (GND_CN11)
unnamed: U1.CN12_9 (GND_CN12), U1.CN12_20 (GND_CN12), U1.CN12_39 (GND_CN12), U1.CN12_54 (GND_CN12), U1.CN12_63 (GND_CN12), U1.CN12_71 (GND_CN12), U1.CN12_72 (GND_CN12)

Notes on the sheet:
MCU - Symbol B

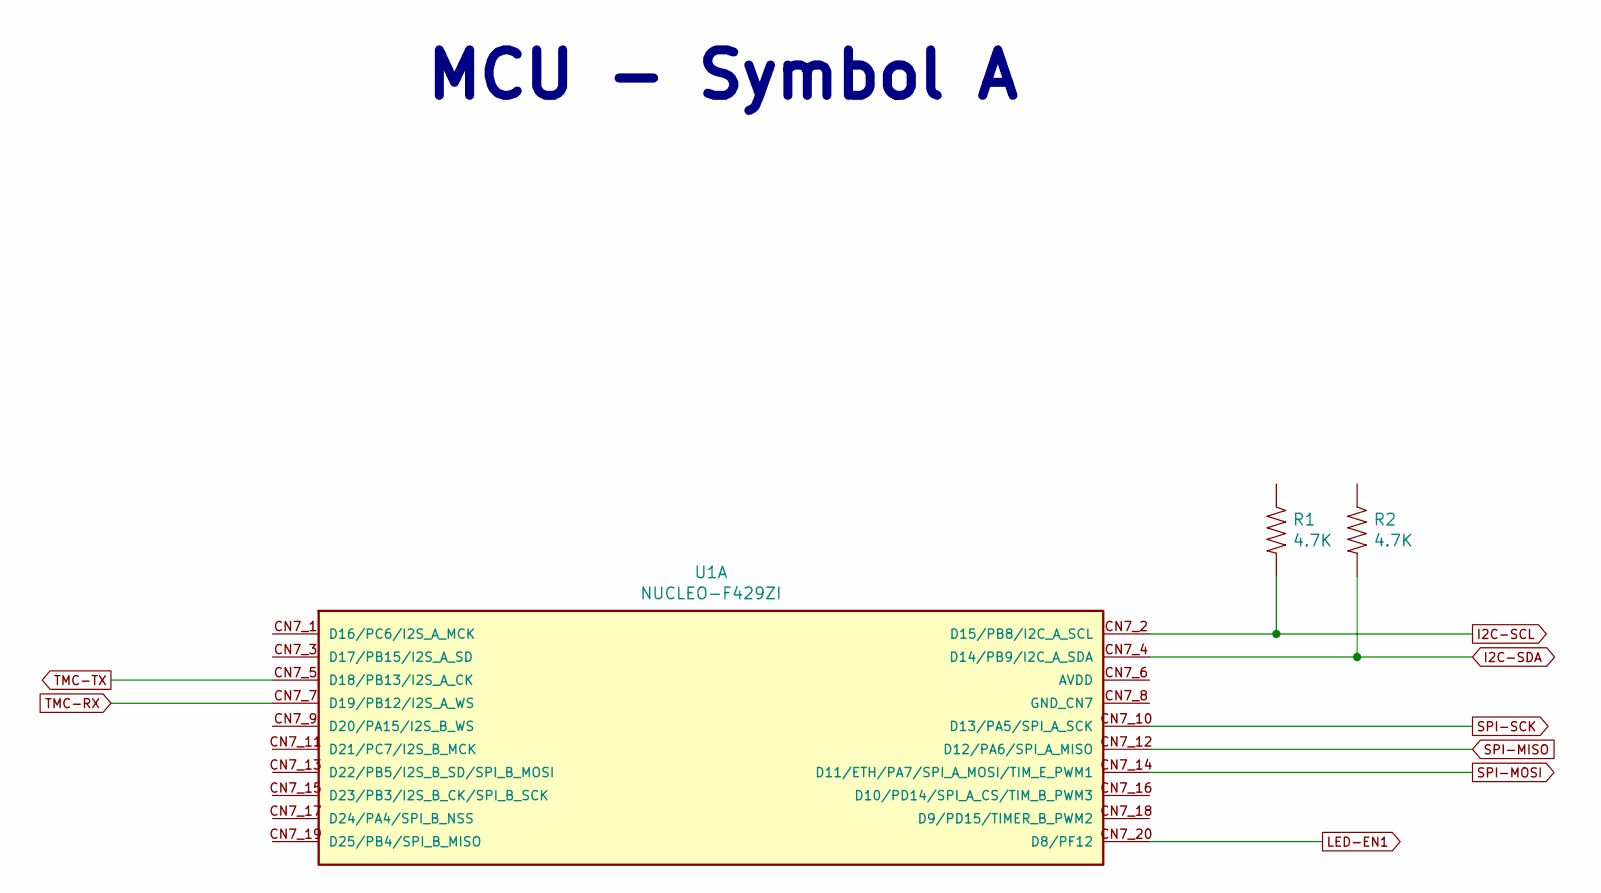
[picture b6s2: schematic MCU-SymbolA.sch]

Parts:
R1, R2: 4.7K; R_0603_1608Metric
U1: NUCLEO-F429ZI; MODULE_NUCLEO-F429ZI

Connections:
I2C-SCL: R1.2, U1.CN7_2 (D15/PB8/I2C_A_SCL)
I2C-SDA: R2.2, U1.CN7_4 (D14/PB9/I2C_A_SDA)
LED-EN1: U1.CN7_20 (D8/PF12); also elsewhere on the board
unnamed: U1.CN9_12 (GND_CN9), U1.CN9_23 (GND_CN9)
unnamed: U1.CN10_5 (GND_CN10), U1.CN10_17 (GND_CN10), U1.CN10_22 (GND_CN10), U1.CN10_27 (GND_CN10)
unnamed: U1.CN11_8 (GND_CN11), U1.CN11_19 (GND_CN11), U1.CN11_20 (GND_CN11), U1.CN11_22 (GND_CN11), U1.CN11_49 (GND_CN11), U1.CN11_60 (GND_CN11), U1.CN11_71 (GND_CN11), U1.CN11_72 (GND_CN11)
unnamed: U1.CN12_9 (GND_CN12), U1.CN12_20 (GND_CN12), U1.CN12_39 (GND_CN12), U1.CN12_54 (GND_CN12), U1.CN12_63 (GND_CN12), U1.CN12_71 (GND_CN12), U1.CN12_72 (GND_CN12)

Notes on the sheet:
MCU - Symbol A
